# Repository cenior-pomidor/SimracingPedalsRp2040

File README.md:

# 🏎️ SimPedal Brake — Тормозная педаль для сим-рейсинга

> Открытый проект тормозной педали для симуляторов гонок на базе **RP2040** и **24-битного АЦП ADS1220** с тензодатчиком (load cell) на 100 кг.

---

## 📋 Описание

**SimPedal Brake** — это высокоточная USB тормозная педаль для гоночных симуляторов, основанная на измерении силы нажатия тензодатчиком. В отличие от потенциометрических педалей, тензодатчик измеряет **усилие**, а не перемещение, что обеспечивает реалистичное торможение, близкое к настоящему гоночному автомобилю.

### Почему этот проект?

- **Доступность** — общая стоимость компонентов ~\$15–25 (без учёта механики и корпуса).
- **Точность** — 24-битный АЦП ADS1220 с PGA ×128 обеспечивает разрешение, недостижимое для встроенных 10/12-битных АЦП.
- **Низкая задержка** — USB HID 1000 Гц (опрос каждые 1 мс), внутренняя частота измерений 330 SPS.
- **Продвинутая фильтрация шума** — 6 алгоритмов (One-Euro, Баттерворт, Калман, Медианный, EMA, SMA) + пре-фильтр Анти-выброс с отображением точной задержки в мс.
- **Чистая разводка PCB** — 2-слойная плата с раздельной цифровой и аналоговой землёй (Star Ground), прошедшая геометрический DRC/LVS.
- **Открытость** — схемы, прошивка, конфигуратор и документация по PCB — всё в открытом доступе.

---

## ✨ Возможности

- 🎯 **24-битное разрешение** — АЦП ADS1220 с усилением PGA ×128
- ⚡ **1000 Гц USB HID** — минимальная задержка ввода (1 мс)
- 🔧 **Калибровка** — автоматическая калибровка минимума и максимума
- 🔇 **6 цифровых фильтров + Anti-Spike** — One-Euro (адаптивный), Баттерворт 2-го порядка, Калман 1D, Медианный, EMA, SMA и медианный пре-фильтр ×3 от импульсных помех
- ⏱️ **Контроль задержки (Latency)** — конфигуратор в реальном времени рассчитывает задержку фильтра и всего тракта (АЦП + Фильтр + USB) в миллисекундах
- 📈 **Кривые отклика** — линейная, прогрессивная, дегрессивная (с живой точкой на графике)
- 🛡️ **Ратиометрическое подключение** — подавление шумов питания
- 💾 **Сохранение настроек** — во flash-память RP2040 (CRC32)
- 🖥️ **GUI-конфигуратор** — обновлённый интерфейс с двухканальным осциллографом (до и после фильтра) и встроенным демо-симулятором
- 📡 **Потоковый режим** — вывод телеметрии в реальном времени (100 Гц)
- 🏗️ **Открытая конструкция** — PCB, прошивка и софт под лицензией MIT

---

## 🔩 Необходимые компоненты

<p align="center">
  
  &nbsp;&nbsp;&nbsp;&nbsp;&nbsp;&nbsp;&nbsp;&nbsp;
  
</p>
<p align="center"><i>Waveshare RP2040-Zero (слева) и модуль АЦП ADS1220 (справа)</i></p>

| Компонент | Описание | Примерная цена | Где купить |
|-----------|----------|---------------|------------|
| **Waveshare RP2040-Zero** | Микроконтроллер RP2040, USB-C | ~\$3.50 | [AliExpress](https://aliexpress.com/item/1005004644515880.html), [Waveshare](https://www.waveshare.com/rp2040-zero.htm) |
| **ADS1220 модуль** | 24-битный АЦП, breakout board | ~\$5.00 | [AliExpress](https://aliexpress.com/), [eBay](https://ebay.com/) |
| **Тензодатчик 100 кг** | Полномостовой (Wheatstone bridge) | ~\$5–10 | [AliExpress](https://aliexpress.com/) — поиск «100kg load cell» |
| **Несущая PCB** | Печатная плата проекта (см. docs/) | ~\$2 (за 5 шт.) | [JLCPCB](https://jlcpcb.com/), [PCBWay](https://pcbway.com/) |
| **Пассивные компоненты** | Резисторы, конденсаторы, ферритовая бусина | ~\$1–2 | [LCSC](https://lcsc.com/), [AliExpress](https://aliexpress.com/) |
| **Разъёмы** | Pin headers, клеммная колодка 4-pin | ~\$0.50 | [AliExpress](https://aliexpress.com/) |
| **Крепёж** | Стойки M3, винты, гайки | ~\$0.50 | Любой хозяйственный магазин |

**Итого: ~\$15–25** (без учёта механической конструкции и корпуса педали).

---

## 🔌 Схема подключения

### Таблица подключений RP2040-Zero → ADS1220

```
┌──────────────────────────────────────────────────────────┐
│          RP2040-Zero  ──────►  ADS1220 Module            │
├──────────────┬───────────────────┬───────────────────────┤
│  Пин RP2040  │   Функция        │  Пин ADS1220          │
├──────────────┼───────────────────┼───────────────────────┤
│  GP2         │   SPI0 SCK       │  SCLK                 │
│  GP3         │   SPI0 TX        │  MOSI (DIN)           │
│  GP4         │   SPI0 RX        │  MISO (DOUT)          │
│  GP5         │   GPIO (CS)      │  CS̄ (активный LOW)    │
│  GP6         │   GPIO (вход)    │  DRDY (активный LOW)  │
│  3V3         │   Питание 3.3В   │  DVDD                 │
│  3V3         │   через FB+LC    │  AVDD                 │
│  GND         │   Земля          │  DGND, AGND           │
└──────────────┴───────────────────┴───────────────────────┘
```

### Подключение тензодатчика к ADS1220

```
┌──────────────────────────────────────────────────────────┐
│        Тензодатчик  ──────►  ADS1220 Module              │
├─────────────────┬─────────────┬──────────────────────────┤
│  Провод (цвет)  │   Сигнал    │  Подключение             │
├─────────────────┼─────────────┼──────────────────────────┤
│  Красный        │   E+        │  AVDD (возбуждение 3.3В) │
│  Чёрный         │   E−        │  AGND                    │
│  Зелёный        │   S+        │  AIN0 (через 100Ω+100нФ) │
│  Белый          │   S−        │  AIN1 (через 100Ω+100нФ) │
└─────────────────┴─────────────┴──────────────────────────┘
```

> ⚠️ **Внимание:** Цвета проводов тензодатчика могут отличаться у разных производителей. Перед подключением сверьтесь с документацией вашего датчика!

---

## 🔨 Сборка прошивки

### Предварительные требования

- [Pico SDK](https://github.com/raspberrypi/pico-sdk) (v1.5+)
- CMake (≥ 3.13)
- GNU Arm Embedded Toolchain (`arm-none-eabi-gcc`)
- Git

### Установка Pico SDK

```bash
# Клонировать Pico SDK (если ещё не установлен)
git clone https://github.com/raspberrypi/pico-sdk.git
cd pico-sdk
git submodule update --init

# Установить переменную окружения
# Linux / macOS:
export PICO_SDK_PATH=/path/to/pico-sdk

# Windows (PowerShell):
$env:PICO_SDK_PATH = "C:\path\to\pico-sdk"

# Или постоянно через системные переменные
```

### Сборка

```bash
# Перейти в каталог проекта
cd rp2040pedals

# Создать каталог сборки
mkdir build
cd build

# Сгенерировать файлы сборки
cmake ..

# Собрать прошивку
make -j4
```

После успешной сборки в каталоге `build/` появится файл `pedal_brake.uf2`.
Готовая собранная прошивка также уже находится в репозитории: `firmware/dist/pedal_brake.uf2` (и в разделе [Releases](https://github.com/cenior-pomidor/SimracingPedalsRp2040/releases)).

### Прошивка RP2040-Zero

1. **Отключите** RP2040-Zero от USB.
2. **Зажмите** кнопку **BOOT** на модуле.
3. **Удерживая** кнопку, подключите USB-кабель к ПК.
4. **Отпустите** кнопку BOOT — на ПК появится USB-накопитель `RPI-RP2`.
5. **Скопируйте** файл `firmware/dist/pedal_brake.uf2` на этот диск.
6. Устройство автоматически перезагрузится и запустит прошивку.
7. Педаль определится в системе как **HID-джойстик** «SimPedal Brake» и **COM-порт**.

> 💡 **Подсказка:** Для повторной прошивки повторите шаги 1–6. Держать кнопку BOOT при каждой перепрошивке не требуется, если в прошивке реализован программный вход в режим загрузчика.

---

## 🖥️ Конфигуратор (GUI)

Графический конфигуратор позволяет настраивать педаль без ручного ввода команд.

### Запуск конфигуратора

#### Вариант 1: Готовый исполняемый файл .EXE (без установки Python)
В репозитории уже собран автономный исполняемый файл:
- Запустите файл `configurator/dist/SimPedal_Configurator.exe` двойным кликом.

#### Вариант 2: Запуск из исходного кода Python
```bash
# Перейти в каталог конфигуратора
cd configurator

# Установить зависимости Python (pyserial)
pip install -r requirements.txt

# Запустить конфигуратор
python pedal_configurator.py
```

### Возможности конфигуратора

- 📊 **Двухканальный осциллограф реального времени** — сравнение сырого сигнала АЦП (до фильтра) и очищенного выхода (после фильтра) + оценка подавления шума
- ⏱️ **Расчёт задержки фильтра (Latency, мс)** — точный расчёт добавленной задержки, времени установления 95% и общей задержки тракта (`АЦП 3.0 мс + Фильтр + USB 1.0 мс`)
- 🔇 **6 цифровых фильтров очистки шума**:
  - **Адаптивный 1€ (One-Euro)** — минимальный шум при удержании тормоза и околонулевая задержка при резком нажатии
  - **Баттерворт 2-го порядка (LPF)** — крутой спад −40 дБ/дек против ВЧ-помех и фона 50/60 Гц
  - **Фильтр Калмана 1D (Kalman)** — стабилизация удержания давления при случайном гауссовом шуме
  - **Медианный (Anti-Spike)** — устранение импульсных выбросов без размытия фронта
  - **Экспоненциальный (EMA)** и **Скользящее среднее (SMA)**
  - **+ Пре-фильтр Анти-выброс (Медиана ×3)** перед основным фильтром (+3.0 мс)
- 🎮 **Встроенный Демо-симулятор** — позволяет протестировать работу фильтров и задержки без подключённого оборудования
- 🎯 **Мастер калибровки**, **кривые отклика** с живой рабочей точкой, **мёртвая зона** и **запись во Flash**

### Последовательный протокол (для продвинутых пользователей)

Если вы предпочитаете работать через терминал (115200 бод):

```
CMD:PING                  → RSP:PONG:SimPedal:v1.1       # Проверка связи
CMD:GET_RAW               → RSP:RAW:<значение>           # Отфильтрованное значение АЦП
CMD:GET_FORCE             → RSP:FORCE:<0-65535>           # Нормированное усилие
CMD:GET_CONFIG            → RSP:CONFIG:{...}              # Текущие настройки (JSON)
CMD:CAL_MIN               → RSP:OK:CAL_MIN:<значение>     # Калибровка минимума
CMD:CAL_MAX               → RSP:OK:CAL_MAX:<значение>     # Калибровка максимума
CMD:SET_DEADZONE:500      → RSP:OK:DEADZONE:500           # Мёртвая зона (0-10000, в 0.01%)
CMD:SET_FILTER:8          → RSP:OK:FILTER:8               # Интенсивность фильтра (1-32)
CMD:SET_FILTER_TYPE:5     → RSP:OK:FILTER_TYPE:5          # 0=SMA,1=EMA,2=Med,3=Biquad,4=Kalman,5=OneEuro
CMD:SET_SPIKE_FILTER:1    → RSP:OK:SPIKE_FILTER:1         # 0=выкл, 1=анти-выброс медиана x3
CMD:SET_CURVE:1           → RSP:OK:CURVE:1                # 0=линейная, 1=прогр., 2=дегр.
CMD:SET_INVERT:0          → RSP:OK:INVERT:0               # 0=норм., 1=инвертировано
CMD:SAVE                  → RSP:OK:SAVED                  # Сохранить во flash
CMD:LOAD                  → RSP:OK:LOADED                 # Загрузить из flash
CMD:RESET_CAL             → RSP:OK:RESET                  # Сбросить калибровку
CMD:STREAM_ON             → DAT:<flt>,<force>,<raw>@100Hz # Поток (отфильтрованное, сила, сырое)
CMD:STREAM_OFF            → (остановка потока)             # Остановить поток
```

---

## 🏭 Заказ печатных плат

### JLCPCB (рекомендуется)

1. Перейдите на [jlcpcb.com](https://jlcpcb.com/).
2. Нажмите **«Quote Now»** / **«Instant Quote»**.
3. Загрузите готовый архив **Gerber**: `gerber/SimPedal_Brake_Carrier_v1.0_Gerber.zip`.
4. Параметры заказа:

   | Параметр | Значение |
   |----------|----------|
   | Слои | 2 |
   | Размер | 65 × 45 мм |
   | Количество | 5 (минимум) |
   | Толщина | 1.6 мм |
   | Медь | 1 oz |
   | Финиш | HASL (lead-free) |
   | Цвет | Зелёный / Синий / Черный |
   | Маска | С двух сторон |
   | Шелкография | Да |

5. Стоимость: **~\$2 за 5 плат** + доставка (~\$1–5).
6. Срок изготовления: 2–5 рабочих дней + доставка.

### PCBWay (альтернатива)

1. Перейдите на [pcbway.com](https://pcbway.com/).
2. Нажмите **«Quote Now»**.
3. Загрузите Gerber-файлы.
4. Укажите те же параметры, что и для JLCPCB.
5. Стоимость: **~\$5 за 5 плат** + доставка.

> 💡 **Подсказка:** При заказе через JLCPCB можно одновременно заказать SMD-сборку (SMT Assembly) — фабрика сама установит и припаяет SMD-компоненты на плату. Для этого дополнительно загрузите файлы BOM и Pick & Place (CPL).

---

## 🎯 Калибровка

### Пошаговая инструкция

1. **Подключите** педаль к ПК через USB.
2. **Откройте** конфигуратор (`python pedal_configurator.py`) или терминал.
3. **Калибровка минимума** (педаль не нажата):
   - Убедитесь, что на педаль не действует никакое усилие.
   - Отправьте команду `CMD:CAL_MIN` или нажмите кнопку «Калибровать мин.» в конфигураторе.
   - Дождитесь ответа `RSP:OK:CAL_MIN:<значение>`.
4. **Калибровка максимума** (педаль нажата полностью):
   - Нажмите на педаль с **максимальным** усилием, которое вы планируете использовать при вождении.
   - Отправьте команду `CMD:CAL_MAX` или нажмите кнопку «Калибровать макс.».
   - Дождитесь ответа `RSP:OK:CAL_MAX:<значение>`.
5. **Сохраните** настройки: `CMD:SAVE`.
6. **Проверьте** — нажимайте педаль и наблюдайте за значением `FORCE` (0–65535).

### Советы по калибровке

- 🔄 **Повторяйте калибровку** при изменении механической конструкции педали.
- ⏱️ **Дайте педали прогреться** 1–2 минуты перед калибровкой (температурный дрейф тензодатчика).
- 📉 **Мёртвая зона** — установите 1–3% (`CMD:SET_DEADZONE:100` ... `CMD:SET_DEADZONE:300`) для компенсации механического люфта.
- 📈 **Кривая отклика** — попробуйте прогрессивную (`CMD:SET_CURVE:1`) для более реалистичного ощущения торможения.

---

## ❓ Решение проблем

### Педаль не определяется в системе

| Возможная причина | Решение |
|---|---|
| Не прошита прошивка | Прошейте файл `.uf2` (см. раздел «Прошивка RP2040-Zero») |
| Неисправный USB-кабель | Попробуйте другой кабель (не все USB-C кабели передают данные!) |
| Неисправный USB-порт | Попробуйте другой порт ПК |
| Конфликт драйверов | Переустановите драйвер CDC (Windows: Диспетчер устройств → COM-порты) |

### Значение АЦП не меняется при нажатии

| Возможная причина | Решение |
|---|---|
| Не подключён тензодатчик | Проверьте подключение проводов к клеммной колодке J3 |
| Перепутаны провода | Сверьте цвета проводов с даташитом вашего тензодатчика |
| Нет SPI-связи с ADS1220 | Проверьте пайку SPI-пинов (GP2–GP5), `CMD:PING` должен возвращать `RSP:PONG` |
| ADS1220 не получает питание | Мультиметром проверьте DVDD и AVDD на модуле (должно быть ~3.3 В) |

### Шумный / нестабильный сигнал

| Возможная причина | Решение |
|---|---|
| Плохой контакт проводов | Затяните винты клеммной колодки, проверьте пайку |
| Отсутствуют RC-фильтры | Проверьте установку R1, R2, C6, C7 |
| Нет ферритовой бусины | Установите FB1 для разделения аналогового и цифрового питания |
| Длинные провода тензодатчика | Используйте экранированный кабель, экран подключите к AGND |
| Механические вибрации | Увеличьте размер фильтра: `CMD:SET_FILTER:16` или `CMD:SET_FILTER:32` |
| Помехи от мотора / блока питания | Проверьте заземление, используйте USB-изолятор при необходимости |

### Значение `FORCE` всегда 0 или 65535

| Возможная причина | Решение |
|---|---|
| Не выполнена калибровка | Выполните калибровку (см. раздел «Калибровка») |
| Перепутаны S+ и S− | Поменяйте местами зелёный и белый провода, или используйте `CMD:SET_INVERT:1` |
| Тензодатчик повреждён | Мультиметром проверьте сопротивление моста: E+↔E− и S+↔S− должны быть ~350–1000 Ом |

### COM-порт не доступен

| Возможная причина | Решение |
|---|---|
| Порт занят другой программой | Закройте все терминалы и программы, использующие этот COM-порт |
| Нет прав доступа (Linux) | `sudo usermod -a -G dialout $USER`, перезайдите в систему |
| Не установлен драйвер CDC | Windows: установите драйвер CDC (обычно устанавливается автоматически) |

### Конфигуратор не запускается

| Возможная причина | Решение |
|---|---|
| Не установлен Python | Установите Python 3.8+ с [python.org](https://python.org) |
| Не установлены зависимости | Выполните `pip install -r requirements.txt` |
| Ошибка `ModuleNotFoundError` | Убедитесь, что устанавливаете в правильное виртуальное окружение |

---

## 📁 Структура проекта

```
rp2040pedals/
├── README.md                           # Полное руководство по сборке, прошивке и настройке
├── .gitignore
├── firmware/                           # Исходный код прошивки RP2040 (C / Pico SDK)
│   ├── CMakeLists.txt                  # Файл сборки CMake
│   ├── pico_sdk_import.cmake           # Скрипт подключения SDK
│   ├── dist/
│   │   └── pedal_brake.uf2             # Готовый файл прошивки для RP2040-Zero
│   └── src/
│       ├── main.c                      # Точка входа (HID 1000 Гц, опрос АЦП, TinyUSB)
│       ├── tusb_config.h               # Конфигурация TinyUSB (композит CDC + HID)
│       ├── usb_descriptors.c / .h      # USB HID + CDC дескрипторы
│       ├── ads1220.c / .h              # Драйвер АЦП ADS1220
│       ├── filter.c / .h               # Цифровые фильтры (One-Euro, Biquad, Kalman, Median, EMA, SMA)
│       ├── config.c / .h               # Чтение/запись настроек во flash-память (CRC32)
│       └── protocol.c / .h             # Обработка команд CDC протокола
├── configurator/                       # Программа настройки для ПК (GUI)
│   ├── requirements.txt                # Зависимости Python (pyserial)
│   ├── pedal_configurator.py           # GUI-конфигуратор (Tkinter)
│   └── dist/
│       └── SimPedal_Configurator.exe   # Готовый автономный EXE-файл для Windows
├── gerber/                             # Файлы печатной платы для производства
│   ├── SimPedal_Brake_Carrier_v1.0_Gerber.zip  # Готовый ZIP-архив для JLCPCB/PCBWay
│   ├── SimPedal_Brake_Carrier_v1.0-F_Cu.gtl    # Верхний слой меди
│   ├── SimPedal_Brake_Carrier_v1.0-B_Cu.gbl    # Нижний слой меди (DGND/AGND + Star Ground)
│   ├── SimPedal_Brake_Carrier_v1.0-F_Mask.gts  # Верхняя паяльная маска
│   ├── SimPedal_Brake_Carrier_v1.0-B_Mask.gbs  # Нижняя паяльная маска
│   ├── SimPedal_Brake_Carrier_v1.0-F_Silkscreen.gto # Верхняя шелкография
│   ├── SimPedal_Brake_Carrier_v1.0-B_Silkscreen.gbo # Нижняя шелкография
│   ├── SimPedal_Brake_Carrier_v1.0-Edge_Cuts.gko    # Контур платы (65x45 мм)
│   └── SimPedal_Brake_Carrier_v1.0.drl         # Файл сверловки (Excellon)
├── pcb/
│   ├── SimPedal_Brake.kicad_pcb        # Исходный файл KiCad PCB
│   └── netlist_expected.json           # Карта цепей для DRC/LVS-проверки
├── scripts/
│   ├── generate_gerber.py              # Скрипт генерации Gerber и сверловки
│   ├── generate_kicad_pcb.py           # Генератор KiCad PCB файла
│   └── verify_pcb.py                   # Геометрический DRC + LVS-верификатор Gerber
└── docs/
    ├── pcb_design.md                   # Руководство по проектированию печатной платы
    └── images/                         # Фотографии модулей и визуализация разводки
        ├── ads1220_module.jpg
        ├── rp2040_zero.jpg
        ├── pcb_top.png
        └── pcb_bottom.png
```

---

## 📡 USB-идентификация

| Параметр | Значение |
|----------|----------|
| VID | `0x1209` (pid.codes — открытый реестр USB ID) |
| PID | `0xBEEF` |
| Устройство | Composite: HID (Joystick) + CDC (Serial) |
| Продукт | SimPedal Brake |
| Производитель | OpenSimHW |
| HID Report | 2 байта (`uint16_t`, 0–65535, ось тормоза) |
| HID Poll Rate | 1 мс (1000 Гц) |
| CDC Baud | 115200 |

---

## 📄 Лицензия

```
MIT License

Copyright (c) 2024 OpenSimHW

Данная лицензия разрешает безвозмездно любому лицу, получившему копию
данного программного обеспечения и сопутствующей документации
(далее — «Программное обеспечение»), использовать Программное обеспечение
без ограничений, включая, без ограничения, права на использование,
копирование, изменение, слияние, публикацию, распространение,
сублицензирование и/или продажу копий Программного обеспечения, а также
разрешать лицам, которым предоставляется Программное обеспечение, делать
это при соблюдении следующих условий:

Указанное выше уведомление об авторском праве и данное уведомление о
разрешении должны быть включены во все копии или существенные части
Программного обеспечения.

ПРОГРАММНОЕ ОБЕСПЕЧЕНИЕ ПРЕДОСТАВЛЯЕТСЯ «КАК ЕСТЬ», БЕЗ КАКИХ-ЛИБО
ГАРАНТИЙ, ЯВНЫХ ИЛИ ПОДРАЗУМЕВАЕМЫХ, ВКЛЮЧАЯ, НО НЕ ОГРАНИЧИВАЯСЬ
ГАРАНТИЯМИ ТОВАРНОЙ ПРИГОДНОСТИ, СООТВЕТСТВИЯ ПО НАЗНАЧЕНИЮ И
НЕНАРУШЕНИЯ ПРАВ. НИ В КАКОМ СЛУЧАЕ АВТОРЫ ИЛИ ПРАВООБЛАДАТЕЛИ НЕ НЕСУТ
ОТВЕТСТВЕННОСТИ ПО ИСКАМ О ВОЗМЕЩЕНИИ УЩЕРБА, УБЫТКОВ ИЛИ ДРУГИХ
ТРЕБОВАНИЙ, БУДЬ ТО В РАМКАХ ДОГОВОРА, ДЕЛИКТА ИЛИ ИНЫМ ОБРАЗОМ,
ВОЗНИКАЮЩИМ ИЗ, В СВЯЗИ С ПРОГРАММНЫМ ОБЕСПЕЧЕНИЕМ ИЛИ ИСПОЛЬЗОВАНИЕМ
ПРОГРАММНОГО ОБЕСПЕЧЕНИЯ ИЛИ ИНЫМИ ДЕЙСТВИЯМИ С НИМ.
```

---

## 🙏 Благодарности

- [Raspberry Pi Foundation](https://www.raspberrypi.org/) — за RP2040 и Pico SDK
- [Texas Instruments](https://www.ti.com/) — за ADS1220 и отличную документацию
- [pid.codes](https://pid.codes/) — за открытые USB VID/PID
- [TinyUSB](https://github.com/hathach/tinyusb) — за USB-стек

---

<p align="center">
  <b>Сделано с ❤️ для сообщества сим-рейсинга</b><br>
  <i>Если проект был вам полезен — поставьте ⭐ на GitHub!</i>
</p>

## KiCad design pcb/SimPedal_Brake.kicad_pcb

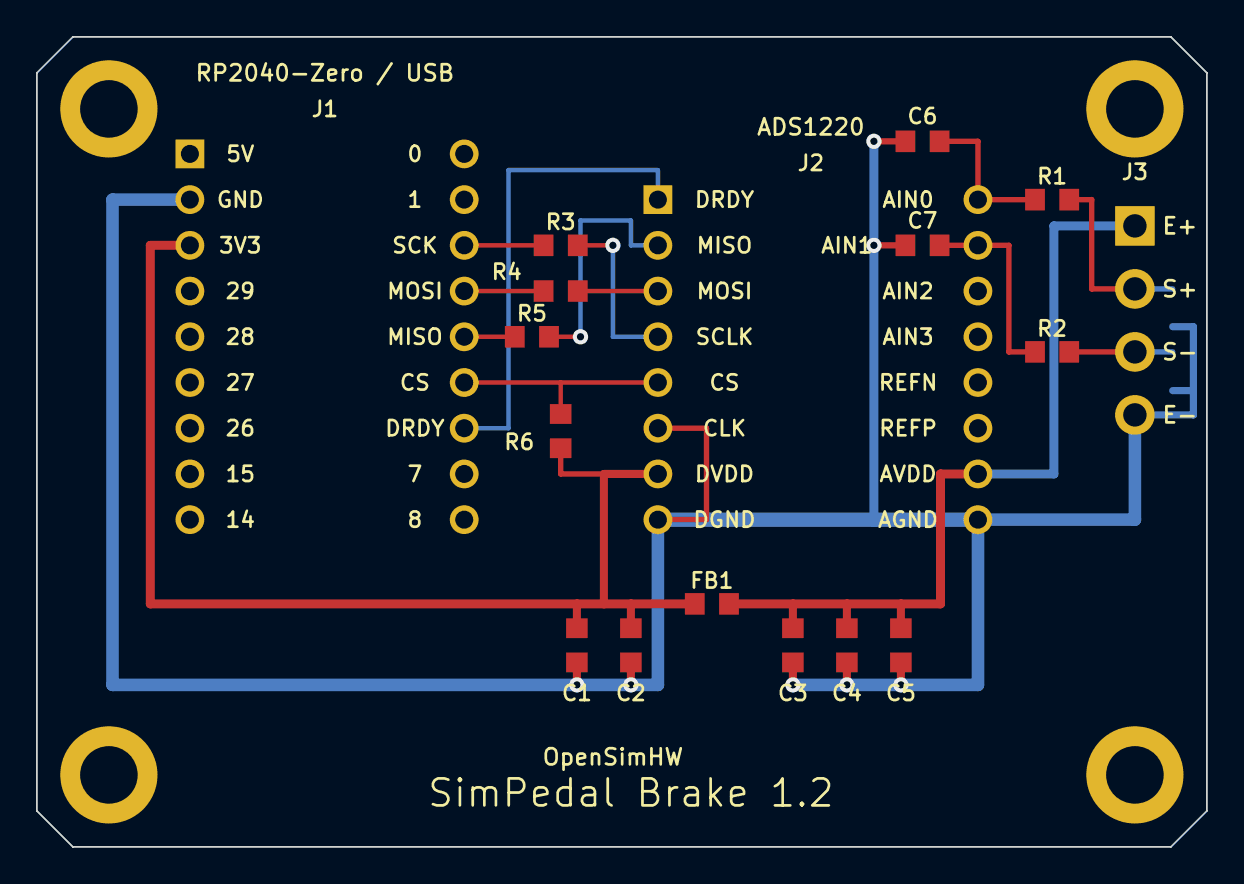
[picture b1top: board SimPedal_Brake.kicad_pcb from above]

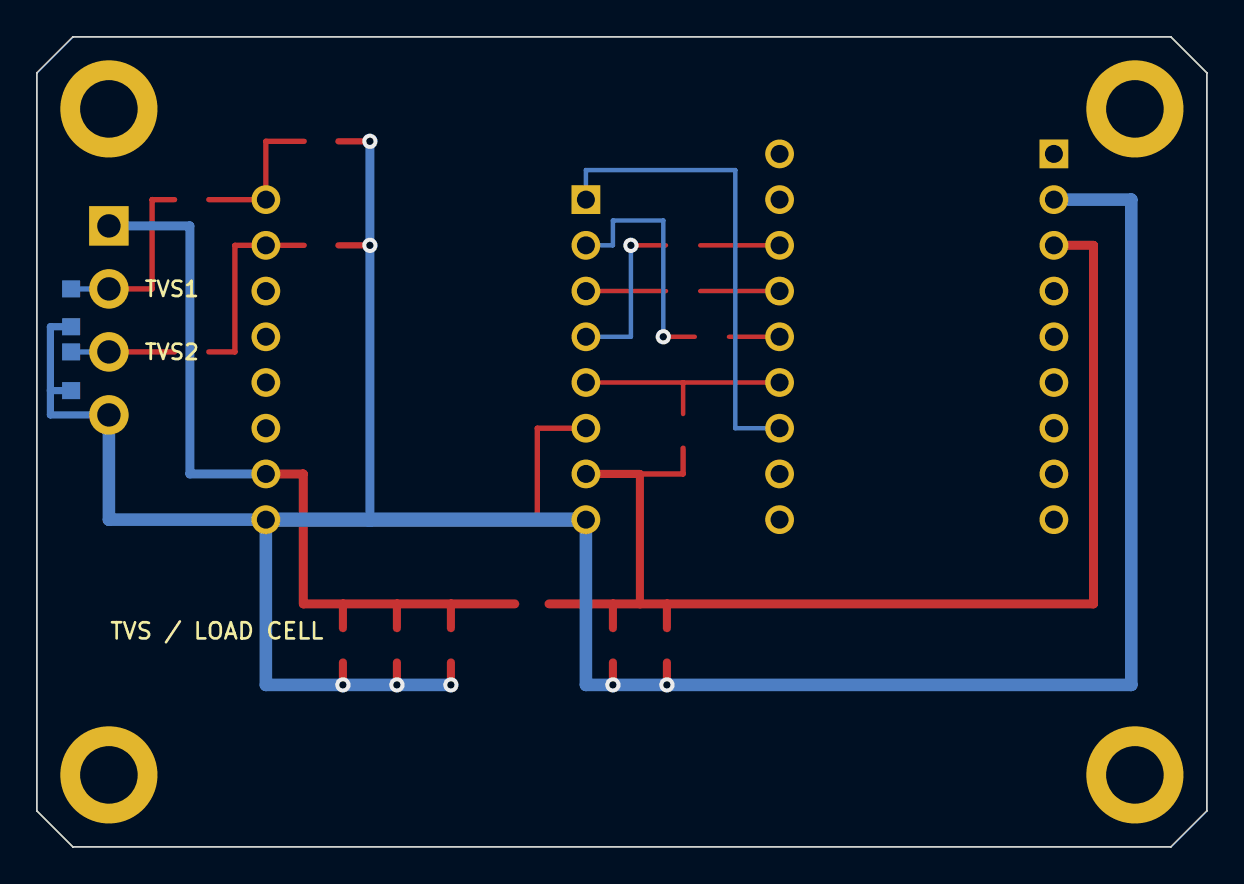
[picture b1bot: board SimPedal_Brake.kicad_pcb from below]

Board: 2 copper layers, 65.0 x 45.0 mm, 23 parts (2 on the bottom side), 15 nets.

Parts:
C1, C3, C6, C7: 100nF; 0805
C2, C4: 10uF; 0805
C5: 1uF; 0805
FB1: 600R @ 100MHz; 0805
H1, H2, H3, H4: Mounting hole M3; Mount_M3
J1: RP2040-Zero
J2: ADS1220
J3: Load cell 3.50mm
R1, R2: 100R; 0805
R3, R4, R5: 33R; 0805
R6: 10k; 0805
TVS1, TVS2: PESD5V0S1BA; SOD-323

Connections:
ADC_AIN0: C6.2, J2.2, R1.1
ADC_AIN1: C7.2, J2.4, R2.1
ADC_DRDY: J1.14, J2.1
AVDD: C3.2, C4.2, C5.2, FB1.2, J2.14, J3.1
DVDD: C1.2, C2.2, FB1.1, J1.5, J2.13, R6.1
GND_SYS: C1.1, C2.1, C3.1, C4.1, C5.1, C6.1, C7.1, J1.3, J2.11, J2.15, J2.16, J3.4, TVS1.2, TVS2.2
LC_SN: J3.3, R2.2, TVS2.1
LC_SP: J3.2, R1.2, TVS1.1
SPI_CS: J1.12, J2.9, R6.2
SPI_MISO_ADC: J2.3, R5.2
SPI_MISO_RP: J1.10, R5.1
SPI_MOSI_ADC: J2.5, R4.2
SPI_MOSI_RP: J1.8, R4.1
SPI_SCK_ADC: J2.7, R3.2
SPI_SCK_RP: J1.6, R3.1
